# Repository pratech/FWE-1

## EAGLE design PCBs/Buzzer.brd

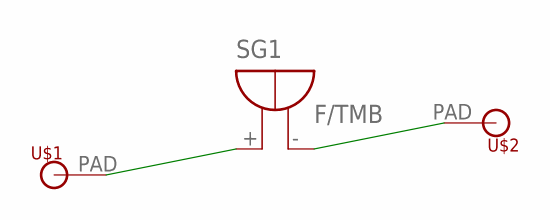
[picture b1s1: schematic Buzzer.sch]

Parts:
SG1: F/TMB
U$1, U$2: MICROBIT_PAD

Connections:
unnamed: SG1.+, U$1.PAD
unnamed: SG1.-, U$2.PAD

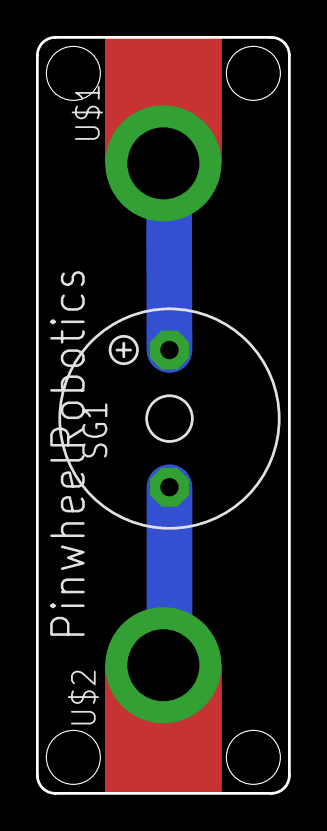
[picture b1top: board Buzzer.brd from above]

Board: 2 copper layers, 14.0 x 42.0 mm, 3 parts (0 on the bottom side), 2 nets.

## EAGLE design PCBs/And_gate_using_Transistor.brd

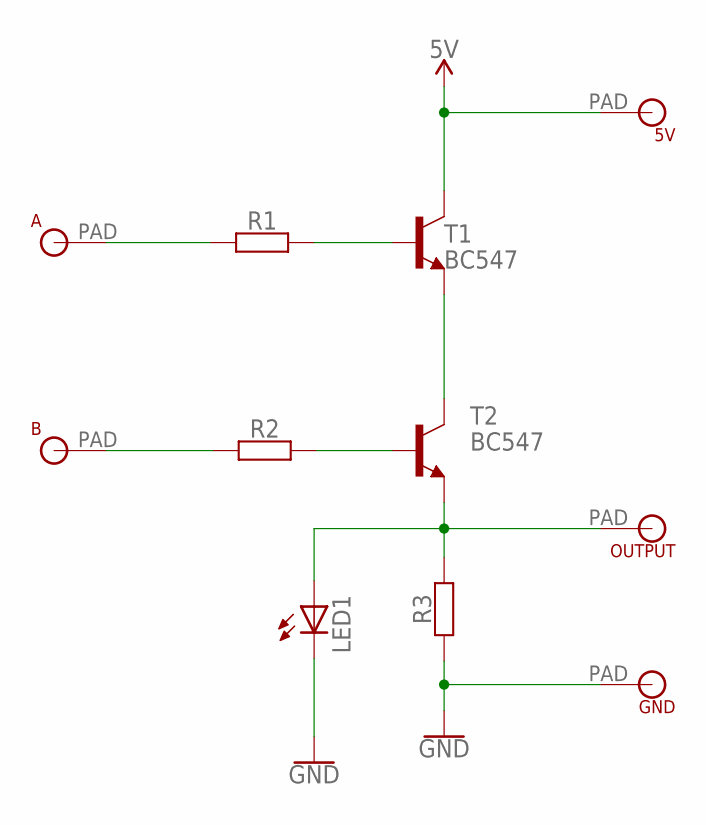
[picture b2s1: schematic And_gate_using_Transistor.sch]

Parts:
5V: MICROBIT_PAD
A: MICROBIT_PAD
B: MICROBIT_PAD
GND: MICROBIT_PAD
LED1: LED3MM
OUTPUT: MICROBIT_PAD
R1, R2, R3: RESISTOR-07; R0207/7
T1, T2: BC547; TO92

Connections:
5V: 5V.PAD, T1.3 (C)
GND: GND.PAD, LED1.K (C), R3.1
unnamed: R2.2, T2.2 (B)
unnamed: T1.1 (E), T2.3 (C)
unnamed: LED1.A, OUTPUT.PAD, R3.2, T2.1 (E)
unnamed: R1.2, T1.2 (B)
unnamed: A.PAD, R1.1
unnamed: B.PAD, R2.1

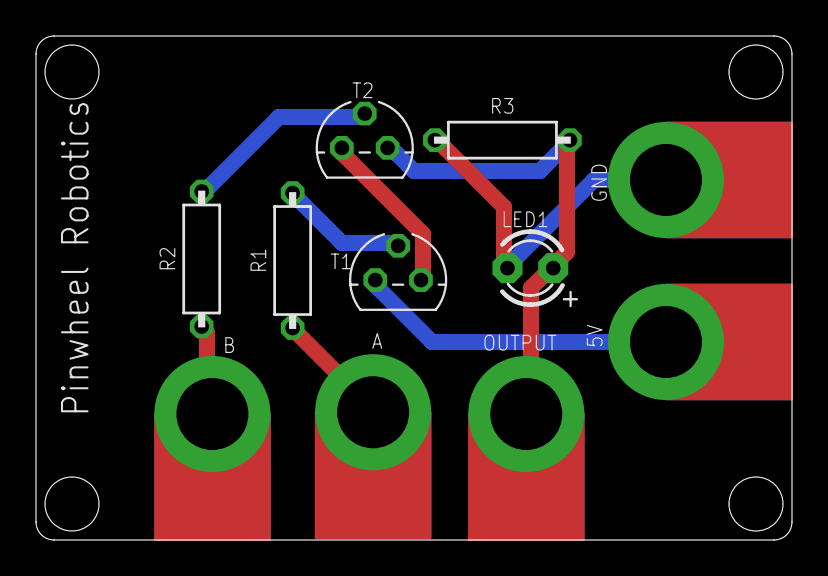
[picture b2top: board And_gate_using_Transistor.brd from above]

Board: 2 copper layers, 42.0 x 28.0 mm, 11 parts (0 on the bottom side), 8 nets.

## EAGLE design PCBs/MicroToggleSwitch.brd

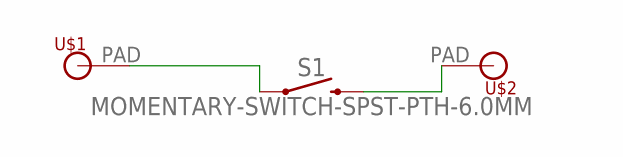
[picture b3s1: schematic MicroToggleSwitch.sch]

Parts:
S1: MOMENTARY-SWITCH-SPST-PTH-6.0MM; TACTILE_SWITCH_PTH_6.0MM
U$1, U$2: MICROBIT_PAD

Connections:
unnamed: S1.1, U$1.PAD
unnamed: S1.3 (2), U$2.PAD

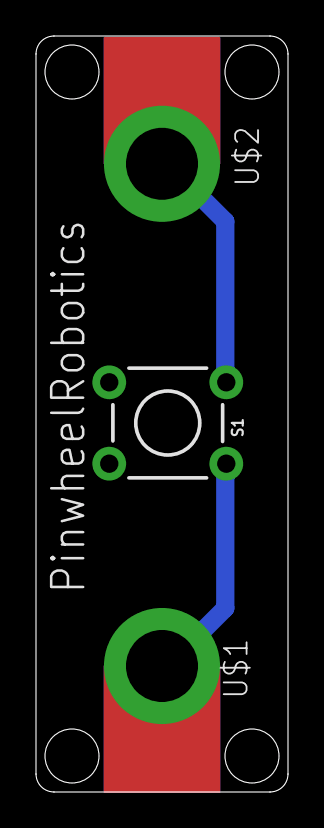
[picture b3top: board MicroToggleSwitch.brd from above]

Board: 2 copper layers, 14.0 x 42.0 mm, 3 parts (0 on the bottom side), 2 nets.

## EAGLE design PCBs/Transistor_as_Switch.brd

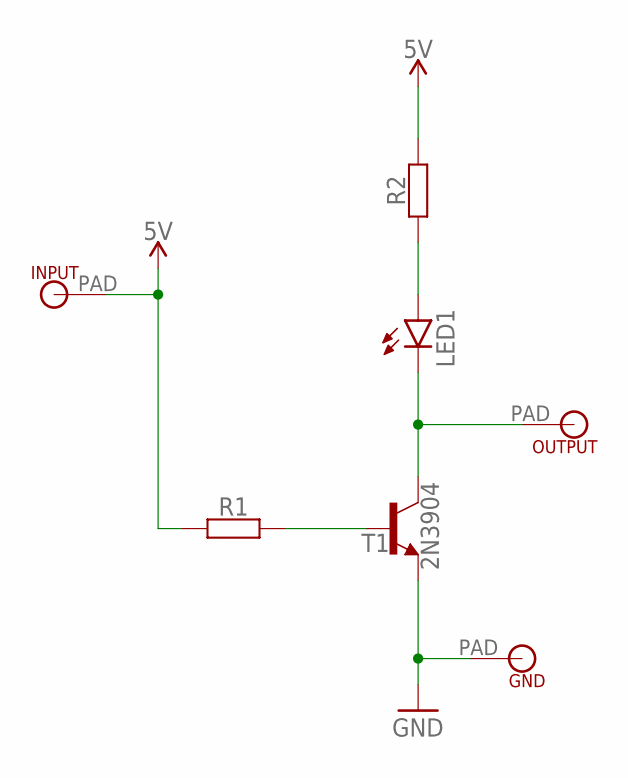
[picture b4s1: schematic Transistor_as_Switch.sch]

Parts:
GND: MICROBIT_PAD
INPUT: MICROBIT_PAD
LED1: LEDCHIP-LED0805; CHIP-LED0805
OUTPUT: MICROBIT_PAD
R1, R2: RESISTOR-10; R0207/10
T1: 2N3904; TO92

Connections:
5V: INPUT.PAD, R1.1, R2.2
GND: GND.PAD, T1.3 (E)
unnamed: LED1.A, R2.1
unnamed: LED1.C, OUTPUT.PAD, T1.1 (C)
unnamed: R1.2, T1.2 (B)

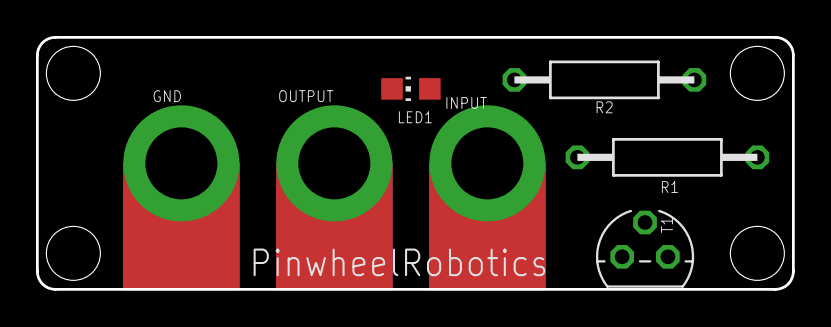
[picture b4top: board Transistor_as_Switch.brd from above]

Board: 2 copper layers, 42.0 x 14.0 mm, 7 parts (0 on the bottom side), 5 nets.

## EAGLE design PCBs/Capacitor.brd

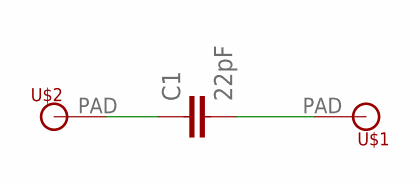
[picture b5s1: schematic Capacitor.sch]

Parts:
C1: 22pF; CAP-PTH-2.54
U$1, U$2: MICROBIT_PAD

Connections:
unnamed: C1.1, U$2.PAD
unnamed: C1.2, U$1.PAD

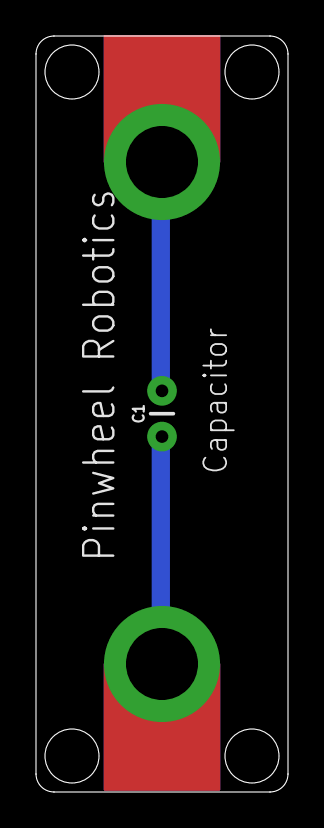
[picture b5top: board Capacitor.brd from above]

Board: 2 copper layers, 14.0 x 42.0 mm, 3 parts (0 on the bottom side), 2 nets.

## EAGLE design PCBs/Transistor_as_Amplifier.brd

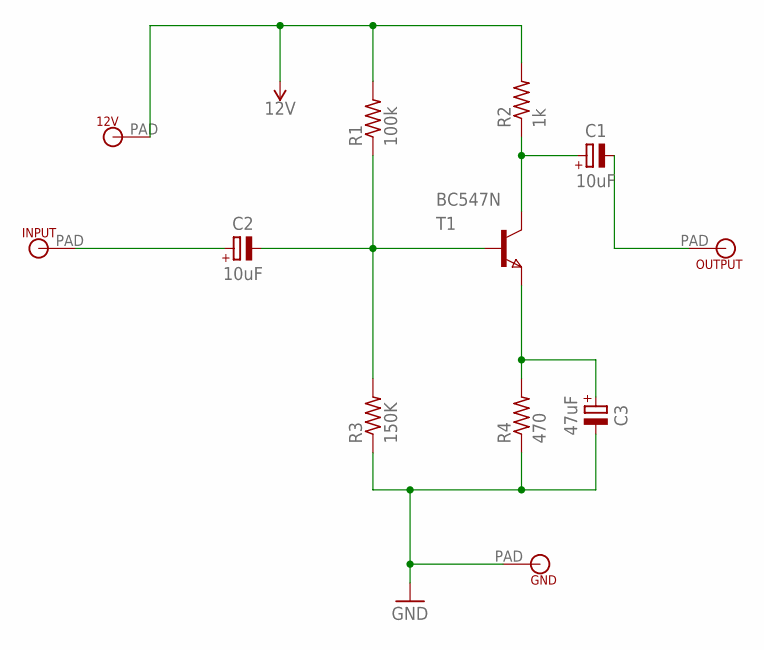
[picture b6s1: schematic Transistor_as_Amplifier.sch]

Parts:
12V: MICROBIT_PAD
C1, C2: 10uF; C_E2-4
C3: 47uF; C_E2-4
GND: MICROBIT_PAD
INPUT: MICROBIT_PAD
OUTPUT: MICROBIT_PAD
R1: 100k; 0207/12
R2: 1k; 0207/12
R3: 150K; 0207/12
R4: 470; 0207/12
T1: BC547N; TO92

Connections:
12V: 12V.PAD, R1.2, R2.2
GND: C3.-, GND.PAD, R3.1, R4.1
unnamed: C3.+, R4.2, T1.3 (E)
unnamed: C1.+, R2.1, T1.1 (C)
unnamed: C2.-, R1.1, R3.2, T1.2 (B)
unnamed: C1.-, OUTPUT.PAD
unnamed: C2.+, INPUT.PAD

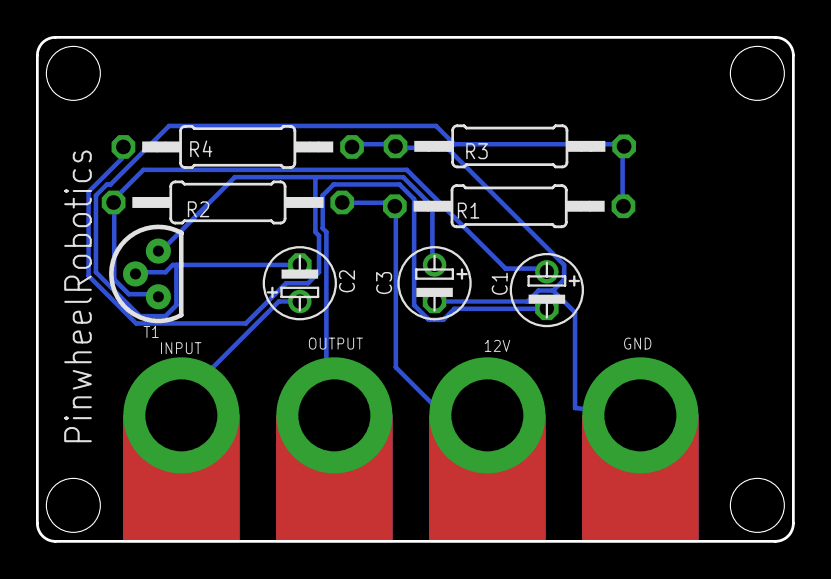
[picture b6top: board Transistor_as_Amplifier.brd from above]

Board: 2 copper layers, 42.0 x 28.0 mm, 12 parts (0 on the bottom side), 7 nets.

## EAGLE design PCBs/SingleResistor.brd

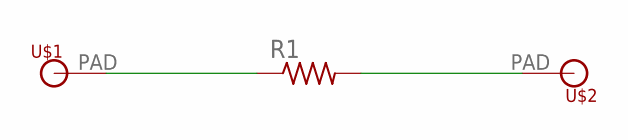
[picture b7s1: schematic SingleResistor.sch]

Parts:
R1: R-US_VMTB60; VMTB60
U$1, U$2: MICROBIT_PAD

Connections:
unnamed: R1.1, U$1.PAD
unnamed: R1.2, U$2.PAD

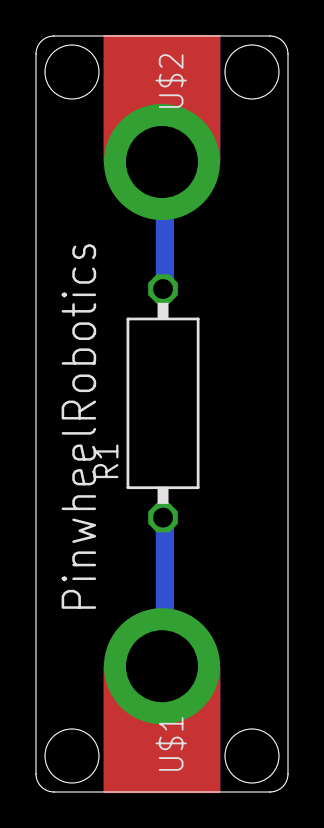
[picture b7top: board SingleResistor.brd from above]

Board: 2 copper layers, 14.0 x 42.0 mm, 3 parts (0 on the bottom side), 2 nets.

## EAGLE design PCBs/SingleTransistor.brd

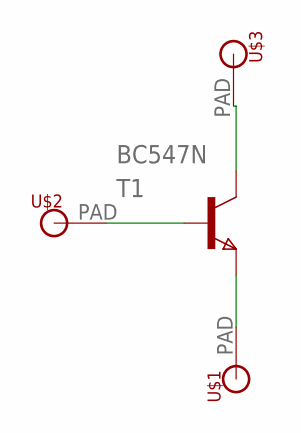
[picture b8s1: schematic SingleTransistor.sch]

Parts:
T1: BC547N; TO92
U$1, U$2, U$3: MICROBIT_PAD

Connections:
unnamed: T1.1 (C), U$3.PAD
unnamed: T1.3 (E), U$1.PAD
T1: T1.2 (B), U$2.PAD

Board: 2 copper layers, 4 parts (0 on the bottom side), 3 nets, no tracks yet.

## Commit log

2024-03-17 Adding First Revision for the design.
2024-07-03 Renamed files .
2024-07-07 Updated 555ic.b#1
2024-07-07 New Design
2024-07-14 updte
2024-07-15 Remove duplicate files and added files at correct location.
2024-07-15 Added Requirements.txt
2024-07-20 New Updates
2024-07-20 New Update
2024-07-31 New Update for board curv
2024-08-18 Dimension added
2024-08-22 Added dimension to the pcb board files.
2024-08-22 Corrected dimesnion for
2024-08-25 Update for Dim width is 42 length is 28 for type 2 pcb
2024-08-27 Corrected hole position for some design , made transistor as switch as category 1
2024-08-27 Combining all Category 1 PCB into single board file.

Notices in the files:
parts and their libraries:
SparkFun-PowerSymbols: Licensing: Creative Commons ShareAlike 4.0 International - https://creativecommons.org/licenses/by-sa/4.0
